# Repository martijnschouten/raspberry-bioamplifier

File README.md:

# Raspberry-bioamplifier
This repository contains the source of a bioamplifier based on a Raspberry Pi Zero w that streams data to matlab. The project was made at the NIFTy group at the University of Twente as a demonstrator for the IEEE student measurement challange at the IEEE conference in Glasgow in 2017. 

(Click image to play video)

To be able to measure the EMG and FMG a bioamplifier shield for the raspberry pi zero w is develloped. The schematic and the layout of the pcb can be found in the bioamplifier folder. This PCB contains an 24 bit ADC, a quad opamp for measurements and one aditional single opamp that can be used as a driven right leg. As this was a prototype, each opamp has many resistors placed around it that do not all have to be soldered. By soldering certain resistors the opamp can be configured as a FMG sensor or as an EMG sensor. The specific configuration used for the demo in Glasgow can be found in the folder "demo configuration"

The data form the adc is read out using an Raspberry Pi Zero W. The program written in c++ used to read out the ADC and send the data to matlab via TCP/IP can be found in the "raspberry code" folder. The matlab scripts used to stream and process the data on the other side can be found in the folder "matlab scripts".

This project has received funding from the European Union’s Horizon 2020 research and innovation programme under grant agreement No. 688857 (SoftPro)

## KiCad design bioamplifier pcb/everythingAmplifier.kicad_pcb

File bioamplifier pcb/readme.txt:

The PCB is designed using Kicad and it's dimensions are such that it can be ordered as a 5x5cm pcb at the big chinese PCB manufacturers.

The PCB contains an 24 bit ADC, a quad opamp for measurements and one aditional single opamp that can be used as a driven right leg. As this was a prototype, each opamp has many resistors placed around it that do not all have to be soldered. By soldering certain resistors the opamp can be configured as for example a FMG sensor or as an EMG sensor.

Bugs and options for improvement:
1. The capacitances (C6-C9) of the low pass filters in front of the ADC result in noise on the analog ground, when high capacitance values are used (1 uF).
2. Daisy chaining the boards is not possible since:
	-No external clock can supplied
	-A mix up of the CS and the DRDY signal...
3. The u.fl connectors are not very reliable, it might be a good idea to replace them mmcx connectors or a 3d printed connector
4. The resolution of the ADC is not fully used due to the large amount of noise. Further research on what is causing this noise is necessary.

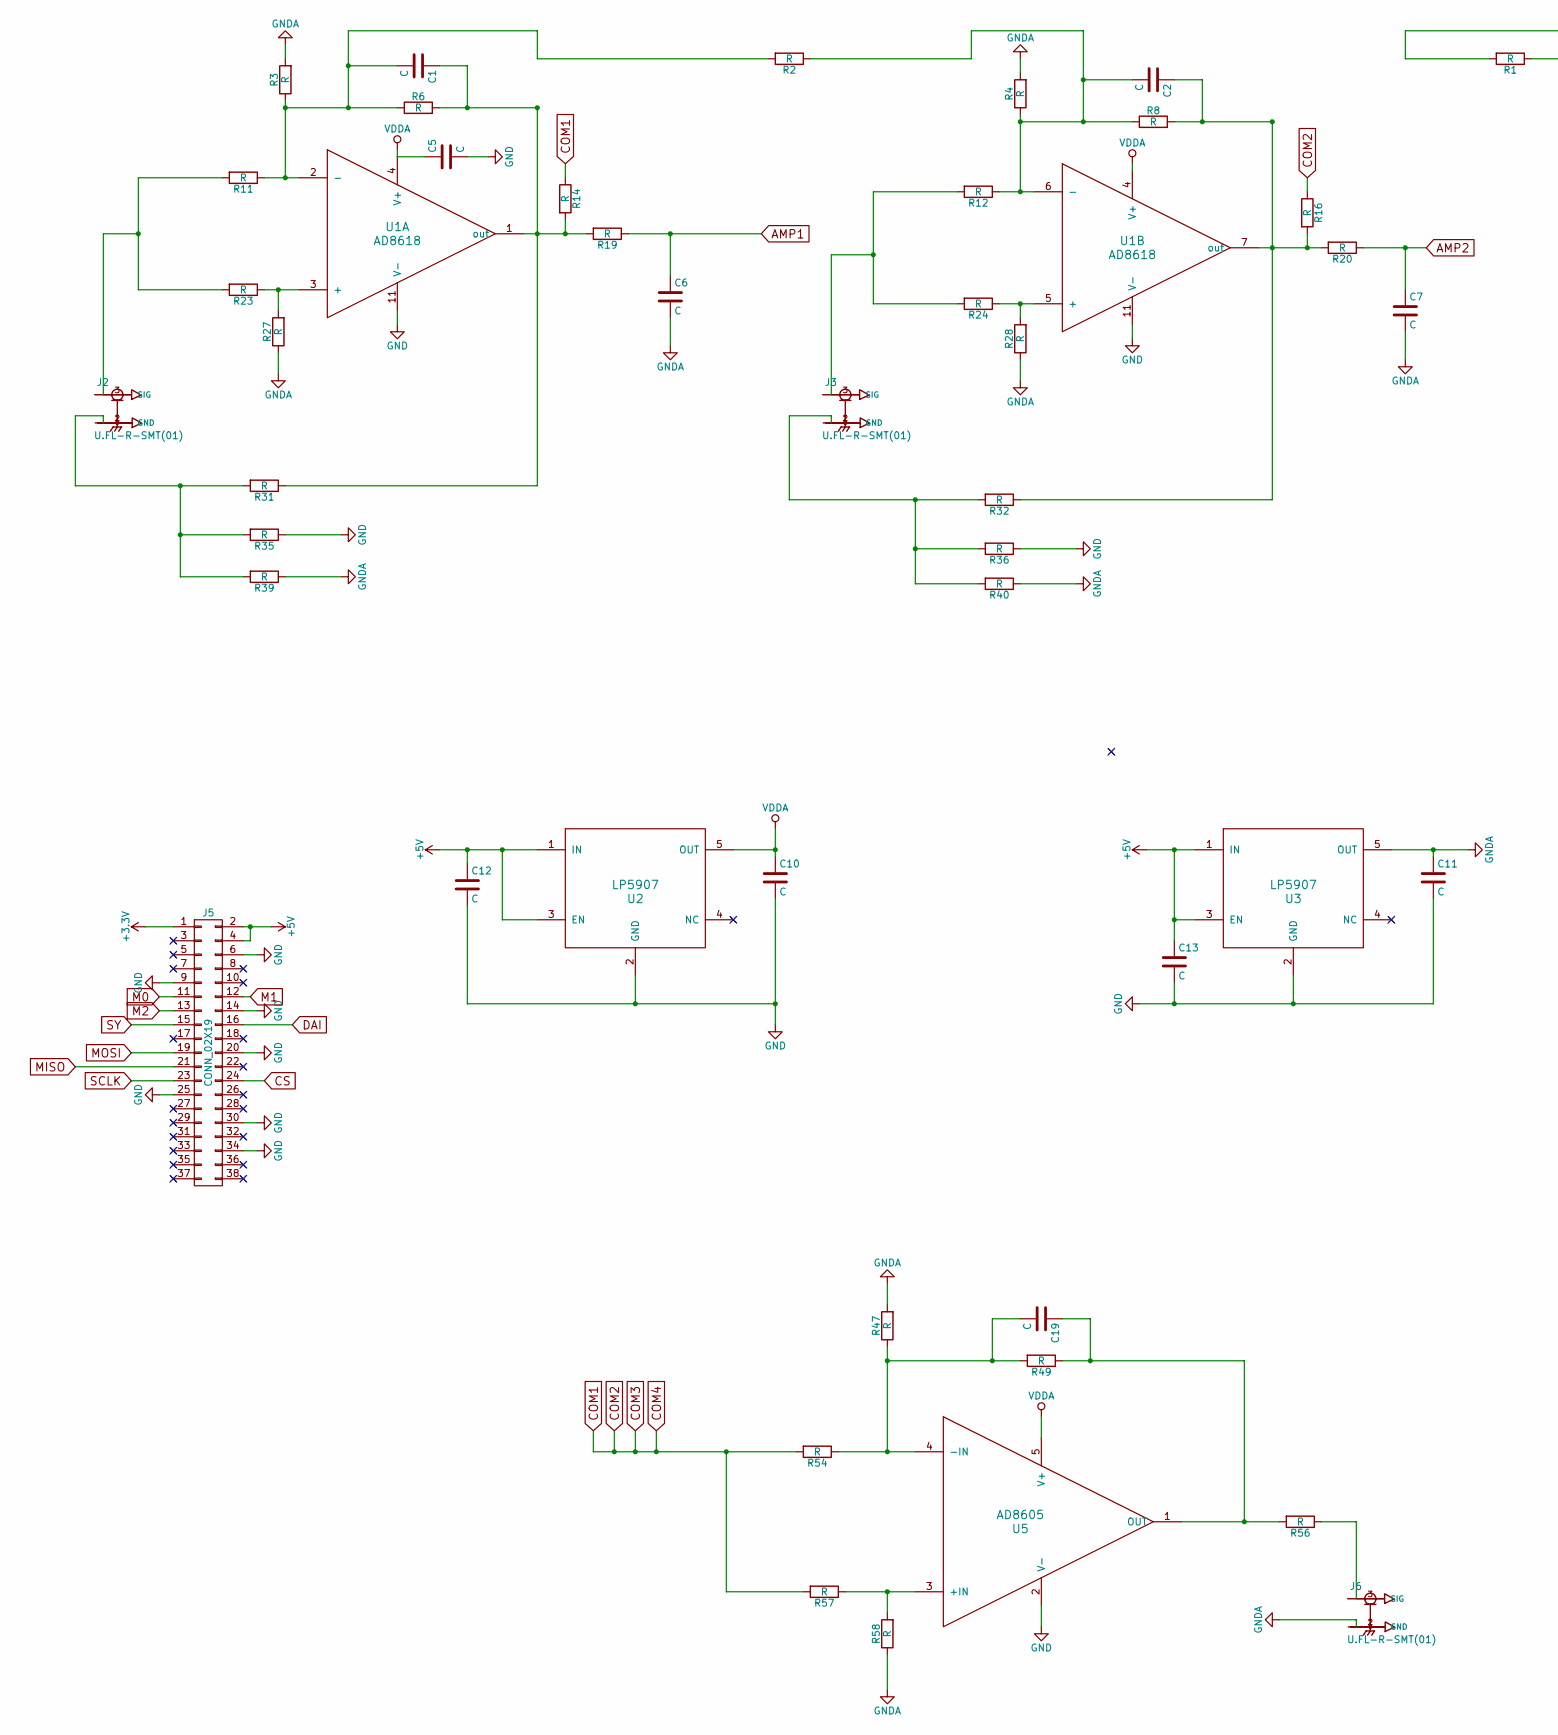
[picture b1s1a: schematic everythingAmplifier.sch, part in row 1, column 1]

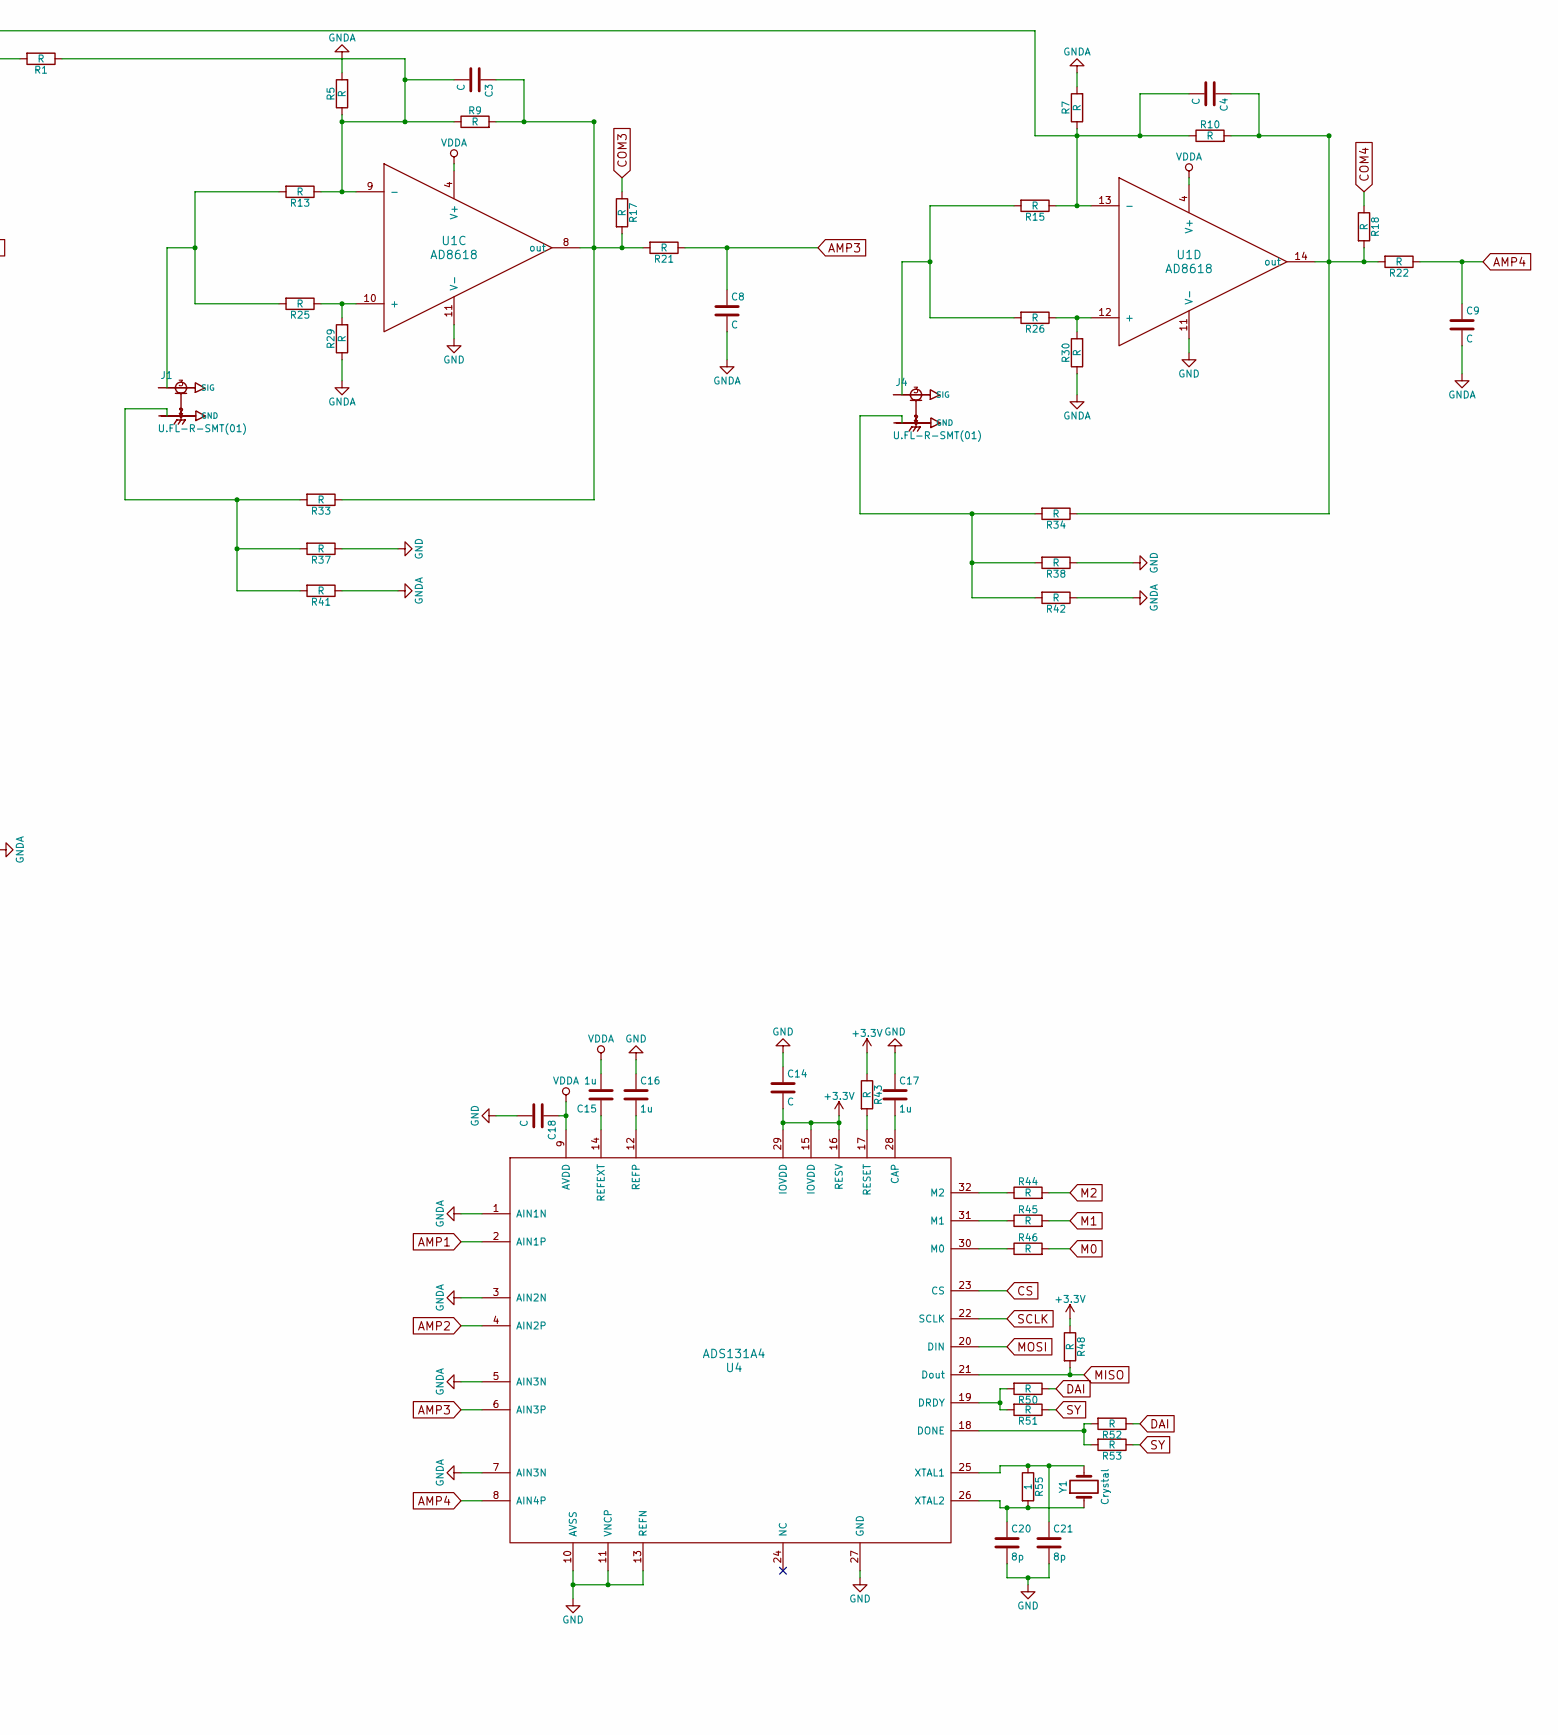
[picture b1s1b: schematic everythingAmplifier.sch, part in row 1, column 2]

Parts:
C1, C2, C3, C4, C5, C6, C7, C8, C9, C10, C11, C12, C13, C14, C18, C19: C; C_0805_HandSoldering
C15, C16, C17: 1u; C_0805_HandSoldering
C20, C21: 8p; C_0805_HandSoldering
J1, J2, J3, J4, J6: U.FL-R-SMT(01); HRS_U.FL-R-SMT(01)
J5: CONN_02X19; Pin_Header_Straight_2x19_Pitch2.54mm
R1, R2, R3, R4, R5, R6, R7, R8, R9, R10, R11, R12, R13, R14, R15, R16, R17, R18, R19, R20, R21, R22, R23, R24, R25, R26, R27, R28, R29, R30, R31, R32, R33, R34, R35, R36, R37, R38, R39, R40, R41, R42, R43, R44, R45, R46, R47, R48, R49, R50, R51, R52, R53, R54, R56, R57, R58: R; R_0805_HandSoldering
R55: 1; R_0805_HandSoldering
U1: AD8618; SOIC-14_N
U2, U3: LP5907; SOT-23-5_HandSoldering
U4: ADS131A4; LQFP-32_5x5mm_Pitch0.5mm
U5: AD8605; SOT-23-5_HandSoldering
Y1: Crystal; Crystal_HC49-4H_Vertical

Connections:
+3V3: C14.2, J5.1, R43.1, R48.1, U4.15 (IOVDD), U4.16 (RESV), U4.29 (IOVDD)
+5V: C12.1, C13.1, J5.2, J5.4, U2.1 (IN), U2.3 (EN), U3.1 (IN), U3.3 (EN)
AMP1: C6.1, R19.1, U4.2 (AIN1P)
AMP2: C7.1, R20.1, U4.4 (AIN2P)
AMP3: C8.1, R21.1, U4.6 (AIN3P)
AMP4: C9.1, R22.1, U4.8 (AIN4P)
COM1: R14.1, R16.1, R17.1, R18.1, R54.2, R57.2
CS: J5.24, U4.23 (CS)
DAI: J5.16, R50.1, R52.1
GND: C5.2, C10.2, C11.2, C12.2, C13.2, C14.1, C16.1, C17.1, C18.2, C20.2, C21.2, J5.6, J5.9, J5.14, J5.20, J5.25, J5.30, J5.34, R35.1, R36.1, R37.1, R38.1, U1.11 (V-), U2.2 (GND), U3.2 (GND), U4.10 (AVSS), U4.11 (VNCP), U4.13 (REFN), U4.27 (GND), U5.2 (V-)
M0: J5.11, R46.2
M1: J5.12, R45.2
M2: J5.13, R44.2
MISO: J5.21, R48.2, U4.21 (Dout)
MOSI: J5.19, U4.20 (DIN)
unnamed: C1.1, R6.2, R14.2, R19.2, R31.1, U1.1 (out)
unnamed: C1.2, R2.2, R3.1, R6.1, R11.1, U1.2 (-)
unnamed: C2.1, R8.2, R16.2, R20.2, R32.1, U1.7 (out)
unnamed: C2.2, R2.1, R4.1, R8.1, R12.1, U1.6 (-)
unnamed: C3.1, R9.2, R17.2, R21.2, R33.1, U1.8 (out)
unnamed: C4.1, R10.2, R18.2, R22.2, R34.1, U1.14 (out)
unnamed: C4.2, R1.2, R7.1, R10.1, R15.1, U1.13 (-)
unnamed: C15.1, U4.14 (REFEXT)
unnamed: C16.2, U4.12 (REFP)
unnamed: C17.2, U4.28 (CAP)
unnamed: C19.1, R49.1, R56.2, U5.1 (OUT)
unnamed: C19.2, R47.1, R49.2, R54.1, U5.4 (-IN)
unnamed: C20.1, R55.2, U4.26 (XTAL2), Y1.1
unnamed: C21.1, R55.1, U4.25 (XTAL1), Y1.2
unnamed: J1.1 (GND), J1.2 (GND), R33.2, R37.2, R41.2
unnamed: J1.3 (SIG), R13.2, R25.2
unnamed: J2.1 (GND), J2.2 (GND), R31.2, R35.2, R39.2
unnamed: J2.3 (SIG), R11.2, R23.2
unnamed: J3.1 (GND), J3.2 (GND), R32.2, R36.2, R40.2
unnamed: J3.3 (SIG), R12.2, R24.2
unnamed: J4.1 (GND), J4.2 (GND), R34.2, R38.2, R42.2
unnamed: J4.3 (SIG), R15.2, R26.2
unnamed: J6.3 (SIG), R56.1
unnamed: R23.1, R27.2, U1.3 (+)
unnamed: R24.1, R28.2, U1.5 (+)
unnamed: R25.1, R29.2, U1.10 (+)
unnamed: R26.1, R30.2, U1.12 (+)
unnamed: R43.2, U4.17 (RESET)
unnamed: R44.1, U4.32 (M2)
unnamed: R45.1, U4.31 (M1)
unnamed: R46.1, U4.30 (M0)
unnamed: R50.2, R51.2, U4.19 (DRDY)
unnamed: R52.2, R53.2, U4.18 (DONE)
unnamed: R57.1, R58.2, U5.3 (+IN)
SCLK: J5.23, U4.22 (SCLK)
SY: J5.15, R51.1, R53.1
VDDA: C5.1, C10.1, C15.2, C18.1, U1.4 (V+), U2.5 (OUT), U4.9 (AVDD), U5.5 (V+)

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
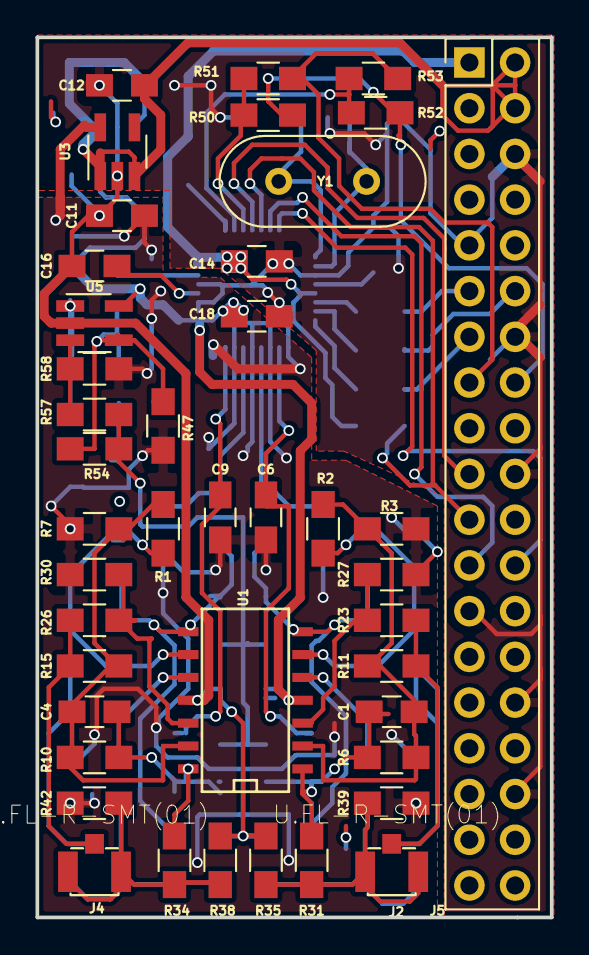
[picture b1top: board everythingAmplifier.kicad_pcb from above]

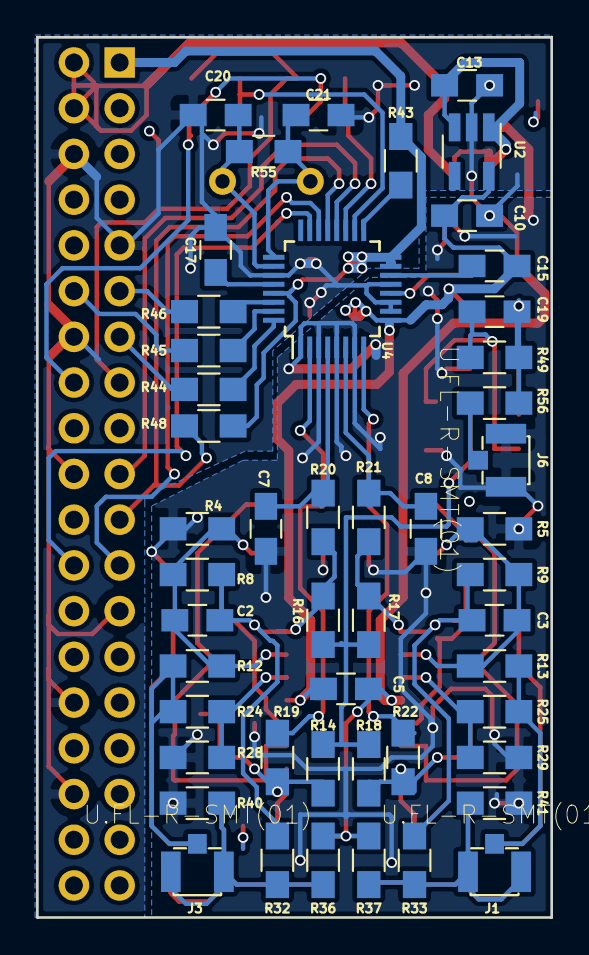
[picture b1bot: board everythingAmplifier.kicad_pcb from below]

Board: 2 copper layers, 28.6 x 48.9 mm, 91 parts (49 on the bottom side), 54 nets.

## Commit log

2017-11-04 added all files
    added all files
2017-11-04 edited pcb readme
    added driven right leg description
2017-11-04 eddited pcb description
    changed name of known bugs such that it appears on github
    added describtion
2017-11-04 updated main description again
2017-11-04 edited readme's
2017-11-05 updated readme's
2017-11-05 added presentation
2017-12-08 added file to plot the measured data
